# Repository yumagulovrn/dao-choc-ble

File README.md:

# Dao Choc BLE Keyboard

Dao Choc BLE keyboard is an ergonomic wireless split keyboard for Kailh Choc switches based on MINEW MS88SF2 BLE module. This split keyboard is similar to Corne but it has an extra keys for brackets and international layouts as on Jorne or Jian.

Available in 44 and 42 key variants

Inspiration for the keyboard was taken from these keyboards:
- [le_chiff_ble](https://github.com/MangoIV/le_chiff_ble) by [MangoIV](https://github.com/MangoIV) - electrical circuit
- [Corne](https://github.com/foostan/crkbd) by [foostan](https://github.com/foostan) - thumb cluster
- [Jorne](https://github.com/joric/jorne) by [joric](https://github.com/joric) - extra pinky key
- [Jian](https://github.com/KGOH/Jian-Info) by [KGOH](https://github.com/KGOH) - extra pinky key and column staggering
- [Coren-ish Zen](https://lowprokb.ca/products/corne-ish-zen) by [DarrylDH](https://github.com/LOWPROKB) - choc-spacing, vibes

## Features

- Hotswapabble
- Long battery life
- ZMK firmware
- Low profile
- Choc Spacing (18mm x 17mm)

## Firmware

Latest compiled ZMK firmware for this keyboard can be found here: https://github.com/yumagulovrn/dao-zmk-config/releases/latest

Source Code: https://github.com/yumagulovrn/dao-zmk-config

## Bootloader

Latest compiled bootloader based on Adafruit nRF52 Bootloader can be found here: https://github.com/yumagulovrn/Adafruit_nRF52_Bootloader/releases/latest

Source code: https://github.com/yumagulovrn/Adafruit_nRF52_Bootloader/tree/dao

You will need separate device to flash the bootloader.

Guide "how to flash the bootloader" can be found [here](https://github.com/Ladniy/jiran-ble-lite/wiki/Firmware). You can literally follow these instructions step-by-step but with *.hex file from [here](https://github.com/yumagulovrn/Adafruit_nRF52_Bootloader/releases/latest)

## Gerbers

https://github.com/yumagulovrn/dao-choc-ble/releases/latest

## BOM

### PCB

| Reference    | Name                      | Package  | Value           | AliExpress                                                                                                                                                                      | LCSC    | Qty |
|--------------|---------------------------|----------|-----------------|---------------------------------------------------------------------------------------------------------------------------------------------------------------------------------|---------|-----|
| BT1          | JST                       | ?        | 1.25mm 2pin 90° | [1.25mm 2pin 90° 50 pcs](https://aliexpress.com/item/10000064127272.html?sku_id=20000000117379413)                                                                              | ?       | 2   |
| C1-C2, C4-C5 | Capacitor                 | 0603     | 10uF            | [10uF - 100 pcs](https://aliexpress.com/item/32966526545.html?sku_id=66569661174)                                                                                               | C19702  | 8   |
| C3           | Capacitor                 | 0603     | 1nF             | [1nF - 100 pcs](https://aliexpress.com/item/32966526545.html?sku_id=66569661147)                                                                                                | C1588   | 2   |
| C6-C7        | Capacitor                 | 0603     | 4.7uF           | [4.7uF 100 pcs](https://aliexpress.com/item/32966526545.html?sku_id=66569661173)                                                                                                | C19666  | 4   |
| D1-D22       | Diode                     | SOD-323  | 1N4148WS        | [1N4148WS SOD-323 - 100 pcs](https://aliexpress.com/item/32849879904.html?sku_id=65195962305)                                                                                   | C57759  | 44  |
| D23          | Diode                     | SOD-123  | 1N5819W         | [1N5819W SOD-123 - 100 pcs](https://aliexpress.com/item/32849879904.html?sku_id=65195962304)                                                                                    | C169540 | 2   |
| D24          | LED                       | 0603     | RED             | [0603 RED - 100 pcs](https://aliexpress.com/item/1206456185.html?sku_id=65106628406)                                                                                            | C2286   | 2   |
| D25          | LED                       | 0603     | BLUE            | [0603 BLUE - 100 pcs](https://aliexpress.com/item/1206456185.html?sku_id=65106628409)                                                                                           | C72041  | 2   |
| F1           | Fuse                      | 1206     | 500mA           | [1206 500mA - 50 pcs](https://aliexpress.com/item/32907456681.html?sku_id=12000033093354867)                                                                                          | C355568 | 2   |
| J1           | USB Receptacle            | ?        | ?               | [1.6mm - 10 pcs](https://aliexpress.com/item/32998900371.html?sku_id=12000021526913497) [0.8mm - 10 pcs](https://aliexpress.com/item/32998900371.html?sku_id=12000021526913496) | C168688 | 2   |
| K1-K22       | Kailh Choc Hotswap Socket | ?        | ?               | [90 pcs](https://aliexpress.com/item/33023283633.html?sku_id=10000000883911874)                                                                                                 | ?       | 44  |
| Q1           | P-Mosfet                  | SOT-23   | AO3401A         | [50 pcs](https://aliexpress.com/item/32990534792.html)                                                                                                                          | C15127  | 2   |
| R1-R2        | Resistor                  | 0603     | 5.1k            | [5.1K - 100 pcs](https://aliexpress.com/item/1005001436923851.html?sku_id=12000016109475028)                                                                                    | C23186  | 4   |
| R3           | Resistor                  | 0603     | 4.7             | [4.7R - 100 pcs](https://aliexpress.com/item/1005001436923851.html?sku_id=12000016109357956)                                                                                    | C23164  | 2   |
| R4           | Resistor                  | 0603     | 1M              | [1M - 100 pcs](https://aliexpress.com/item/1005001436923851.html?sku_id=12000016109475082)                                                                                      | C22935  | 2   |
| R5           | Resistor                  | 0603     | **806k***       | [820K - 100pcs](https://aliexpress.com/item/1005001436923851.html?sku_id=12000016109475080)                                                                                     | C103828 | 2   |
| R6-R7        | Resistor                  | 0603     | 1k              | [1K - 100pcs](https://aliexpress.com/item/1005001436923851.html?sku_id=12000016109475011)                                                                                       | C21190  | 4   |
| R8           | Resistor                  | 0603     | 2M              | [2M - 100pcs](https://aliexpress.com/item/1005001436923851.html?sku_id=12000016109475089)                                                                                       | C22976  | 2   |
| R9           | Resistor                  | 0603     | **RPROG****     | [3.3K - 100pcs](https://aliexpress.com/item/1005001436923851.html?sku_id=12000016109475023)                                                                                     | C22978  | 2   |
| R10          | Resistor                  | 0603     | 100k            | [100K - 100pcs](https://aliexpress.com/item/1005001436923851.html?sku_id=12000016109475058)                                                                                     | C25803  | 2   |
| SW1          | SPDT Switch               | ?        | MSK-12C02       | [50 pcs](https://aliexpress.com/item/4000685483225.html?sku_id=12000020983019153)                                                                                               | C431541 | 2   |
| SW2          | Tactile Button            | ?        | TS-1086E        | [100 pcs](https://aliexpress.com/item/1005001846404680.html)                                                                                                                    | C455276 | 2   |
| U1           | MCU                       | ?        | MINEW MS88SF2   | [1 pcs](https://aliexpress.com/item/4000101935456.html)                                                                                                                      | ?       | 2   |
| U2           | ESD Protection IC         | SOT-23-6 | USBLC6-2SC6     | [USBLC6-2SC6 - 10 pcs](https://aliexpress.com/item/32523780535.html?sku_id=12000027513378590)                                                                                   | C558442 | 2   |
| U3           | Voltage Regulator IC      | SOT-23-5 | XC6220          | [30 pcs](https://aliexpress.com/item/4000271612572.html)                                                                                                                        | C86534  | 2   |
| U4           | Battery Charging IC       | SOT-23-5 | MCP73831        | [10 pcs](https://aliexpress.com/item/32714249253.html)                                                                                                                          | C14879  | 2   |

**806k*** You can replace it with 820k resistor, but voltage sensing circuit (for battery status) will give somewhat invalid values

**RPROG**** Value depends on your battery capacity. For 300mAh battery should be 3.3K

### Other hardware

| Name                           | Qty  | AliExpress                                                                                                                                                 |
|--------------------------------|------|------------------------------------------------------------------------------------------------------------------------------------------------------------|
| LiPo Battery 502035            |    2 | [Global - 2 pcs](https://aliexpress.com/item/1005003717206039.html?sku_id=12000026915285813) [RU - 1 pcs](https://www.chipdip.ru/product/robiton-lp502035) |
| Standoff M2x5mm                |   10 | [M2x5mm - 20 pcs](https://aliexpress.com/item/32597776358.html?sku_id=67114100494)                                                                         |
| Standoff M2x8mm                |    6 | [M2x8mm - 20 pcs](https://aliexpress.com/item/32597776358.html?sku_id=67114100497)                                                                         |
| Screw M2x4mm                   |   32 | [Black M2x4mm - 50 pcs](https://aliexpress.com/item/32806166548.html?sku_id=66702152887)                                                                   |
| Connector JST 1.25mm 2pin Male |    2 | [20 pcs](https://aliexpress.com/item/4000076660477.html)                                                                                                   |
| Silicone Bumpers               | 8-10 | [100 pcs](https://aliexpress.com/item/32912066603.html)                                                                                                    |

## Cases

Dao has a pretty wide choice of cases.

### FR4 Case

Consists of:
* Bottom [42key](https://github.com/yumagulovrn/dao-choc-ble/releases/download/v1.0/pcb_42key-dao-choc-ble-bottom-gerber.zip) [44key](https://github.com/yumagulovrn/dao-choc-ble/releases/download/v1.0/pcb_44key-dao-choc-ble-bottom-gerber.zip)
* Plate [42key](https://github.com/yumagulovrn/dao-choc-ble/releases/download/v1.0/pcb_42key-dao-choc-ble-plate-gerber.zip) [44key](https://github.com/yumagulovrn/dao-choc-ble/releases/download/v1.0/pcb_44key-dao-choc-ble-plate-gerber.zip)
* [Shield](https://github.com/yumagulovrn/dao-choc-ble/releases/download/v1.0/pcb_dao-choc-ble-shield-gerber.zip)

**Note: plate should be 1.2mm thickness, bottom and shield can be any thickness you want (but I suggest 1.6mm)**

### 3D Printed Cases

#### OpenSCAD case from [shirokovroma](https://github.com/shirokovroma)

Has two variants:
* Bumper (you would need to have FR4 or printed plate, bottom and shield)
  * 42 keys [left](https://github.com/yumagulovrn/dao-choc-ble/releases/download/v1.0/3d_42key-bumper-left.stl) [right](https://github.com/yumagulovrn/dao-choc-ble/releases/download/v1.0/3d_42key-bumper-right.stl)
  * 44 keys [left](https://github.com/yumagulovrn/dao-choc-ble/releases/download/v1.0/3d_44key-bumper-left.stl) [right](https://github.com/yumagulovrn/dao-choc-ble/releases/download/v1.0/3d_44key-bumper-right.stl)
* Full (you would need to have FR4 or printed plate and shield)
  * 42 keys [left](https://github.com/yumagulovrn/dao-choc-ble/releases/download/v1.0/3d_42key-case-left.stl) [right](https://github.com/yumagulovrn/dao-choc-ble/releases/download/v1.0/3d_42key-case-right.stl)
  * 44 keys [left](https://github.com/yumagulovrn/dao-choc-ble/releases/download/v1.0/3d_44key-case-left.stl) [right](https://github.com/yumagulovrn/dao-choc-ble/releases/download/v1.0/3d_44key-case-right.stl)

#### [Dao keyboard slim case by Grigory Pavlichenko](https://www.thingiverse.com/thing:5988122)

### CNC cases

#### [Dao Shield by Mposiblee](https://github.com/Mposiblee/DaoShield)

## To Do List
- [x] Add BOM
- [x] Add images
- [x] Add descriptions
- [x] Add references to inspiration sources
- [x] Add link to a firmware
- [x] Add link to a bootloader
- [x] Make release v1.0

## Contacts

Telegram: https://ergonautkb.t.me

Telegram (ru): https://ergonautkb_ru.t.me

## Support and Warranty

lmao

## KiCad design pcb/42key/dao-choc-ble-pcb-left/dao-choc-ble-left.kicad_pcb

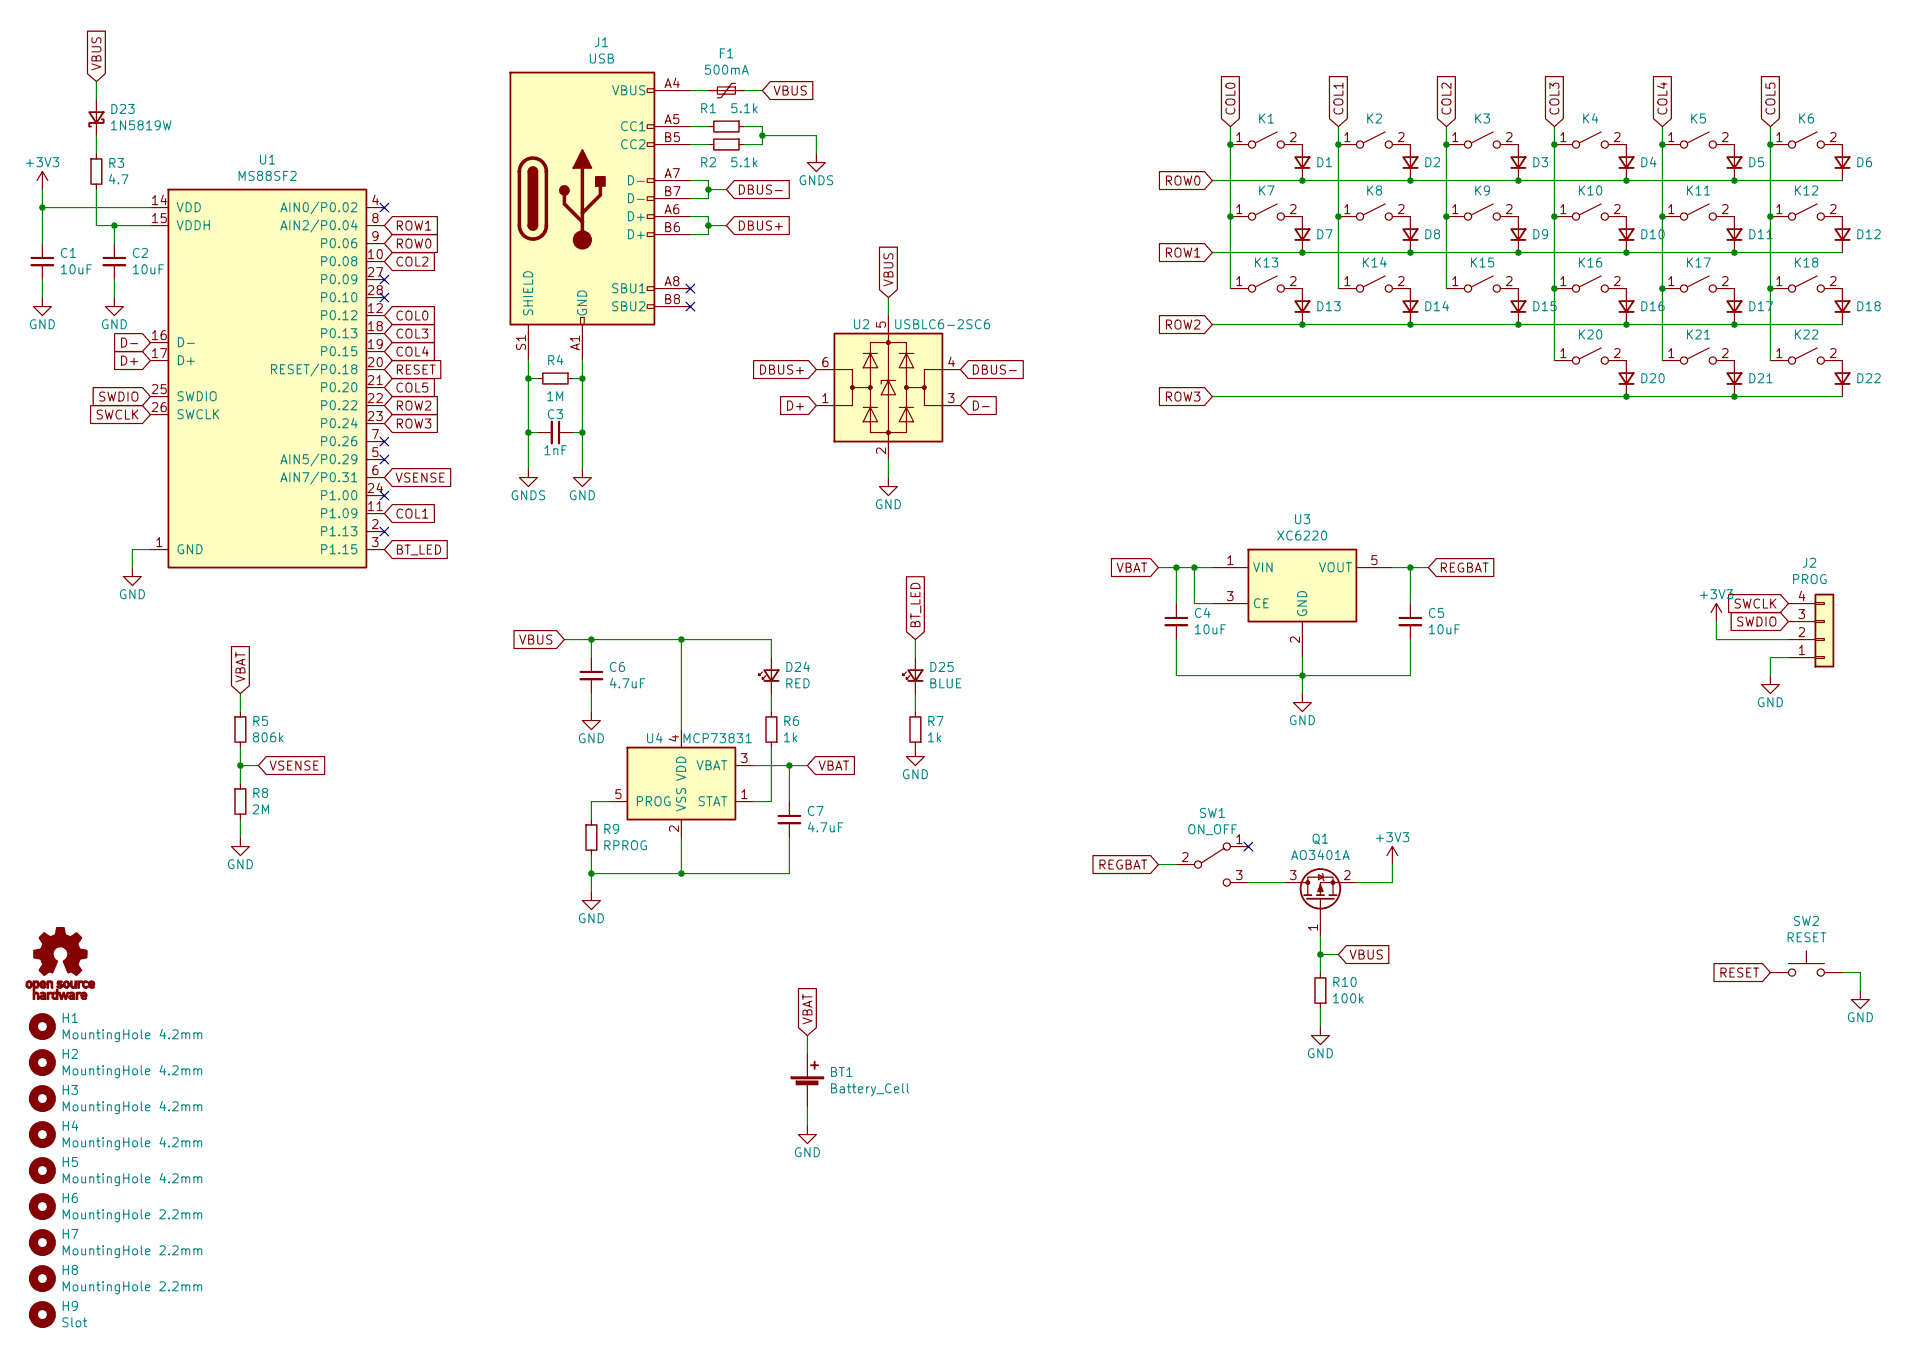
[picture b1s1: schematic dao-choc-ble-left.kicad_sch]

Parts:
BT1: Battery_Cell; Battery
C1, C2, C4, C5: 10uF; C_0603_1608Metric; LCSC C19702
C3: 1nF; C_0603_1608Metric; LCSC C1588
C6, C7: 4.7uF; C_0603_1608Metric; LCSC C19666
D1, D2, D3, D4, D5, D6, D7, D8, D9, D10, D11, D12, D13, D14, D15, D16, D17, D18, D20, D21, D22: 1N4148WS; D_SOD-323; LCSC C57759
D23: 1N5819W; D_SOD-123; LCSC C169540
D24: RED; LED_0603_1608Metric; LCSC C2286
D25: BLUE; LED_0603_1608Metric; LCSC C72041
F1: 500mA; Fuse_1206_3216Metric; LCSC C355568
H1, H2, H3, H4, H5: MountingHole 4.2mm; Hole_4.2mm
H6, H7, H8: MountingHole 2.2mm; Hole_2.2mm
H9: Slot
J1: USB; USB-C_C168688; LCSC C168688
J2: PROG
K1, K2, K3, K4, K5, K6, K7, K8, K9, K10, K11, K12, K13, K14, K15, K16, K17, K18, K20, K21, K22: KEY_SWITCH; Kailh_PG1350_hotswap
LOGO1: OSHW-logo
Q1: AO3401A; SOT-23; LCSC C15127
R1, R2: 5.1k; R_0603_1608Metric; LCSC C23186
R3: 4.7; R_0603_1608Metric; LCSC C23164
R4: 1M; R_0603_1608Metric; LCSC C22935
R5: 806k; R_0603_1608Metric; LCSC C103828
R6, R7: 1k; R_0603_1608Metric; LCSC C21190
R8: 2M; R_0603_1608Metric; LCSC C22976
R9: RPROG; R_0603_1608Metric; LCSC C22978
R10: 100k; R_0603_1608Metric; LCSC C25803
SW1: ON_OFF; MSK-12C02; LCSC C431541
SW2: RESET; TS-1086E; LCSC C455276
U1: MS88SF2; MINEW_MS88SF2
U2: USBLC6-2SC6; SOT-23-6; LCSC C558442
U3: XC6220; SOT-23-5; LCSC C86534
U4: MCP73831; SOT-23-5; LCSC C14879

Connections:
+3V3: C1.1, J2.2, Q1.2 (S), U1.14 (VDD)
BT_LED: D25.2 (A), U1.3 (P1.15)
COL0: K1.1 (A), K7.1 (A), K13.1 (A), U1.12 (P0.12)
COL1: K2.1 (A), K8.1 (A), K14.1 (A), U1.11 (P1.09)
COL2: K3.1 (A), K9.1 (A), K15.1 (A), U1.10 (P0.08)
COL3: K4.1 (A), K10.1 (A), K16.1 (A), K20.1 (A), U1.18 (P0.13)
COL4: K5.1 (A), K11.1 (A), K17.1 (A), K21.1 (A), U1.19 (P0.15)
COL5: K6.1 (A), K12.1 (A), K18.1 (A), K22.1 (A), U1.21 (P0.20)
D+: U1.17 (D+), U2.1 (I/O1)
D-: U1.16 (D-), U2.3 (I/O2)
DBUS+: J1.A6 (D+), J1.B6 (D+), U2.6 (I/O1)
DBUS-: J1.A7 (D-), J1.B7 (D-), U2.4 (I/O2)
GND: BT1.2 (-), C1.2, C2.2, C3.1, C4.2, C5.2, C6.2, C7.2, J1.A1 (GND), J1.A12 (GND), J1.B1 (GND), J1.B12 (GND), J2.1, R4.1, R7.1, R8.2, R9.2, R10.1, SW2.2, U1.1 (GND), U1.13 (GND), U2.2 (GND), U3.2 (GND), U4.2 (VSS)
GNDS: C3.2, J1.S1 (SHIELD), R1.1, R2.1, R4.2
unnamed: C2.1, R3.2, U1.15 (VDDH)
unnamed: D1.2 (A), K1.2 (B)
unnamed: D2.2 (A), K2.2 (B)
unnamed: D3.2 (A), K3.2 (B)
unnamed: D4.2 (A), K4.2 (B)
unnamed: D5.2 (A), K5.2 (B)
unnamed: D6.2 (A), K6.2 (B)
unnamed: D7.2 (A), K7.2 (B)
unnamed: D8.2 (A), K8.2 (B)
unnamed: D9.2 (A), K9.2 (B)
unnamed: D10.2 (A), K10.2 (B)
unnamed: D11.2 (A), K11.2 (B)
unnamed: D12.2 (A), K12.2 (B)
unnamed: D13.2 (A), K13.2 (B)
unnamed: D14.2 (A), K14.2 (B)
unnamed: D15.2 (A), K15.2 (B)
unnamed: D16.2 (A), K16.2 (B)
unnamed: D17.2 (A), K17.2 (B)
unnamed: D18.2 (A), K18.2 (B)
unnamed: D20.2 (A), K20.2 (B)
unnamed: D21.2 (A), K21.2 (B)
unnamed: D22.2 (A), K22.2 (B)
unnamed: D23.1 (K), R3.1
unnamed: D24.1 (K), R6.2
unnamed: D25.1 (K), R7.2
unnamed: F1.2, J1.A4 (VBUS), J1.A9 (VBUS), J1.B4 (VBUS), J1.B9 (VBUS)
unnamed: J1.A5 (CC1), R1.2
unnamed: J1.B5 (CC2), R2.2
unnamed: Q1.3 (D), SW1.3 (C)
unnamed: R6.1, U4.1 (STAT)
unnamed: R9.1, U4.5 (PROG)
REGBAT: C5.1, SW1.2 (B), U3.5 (VOUT)
RESET: SW2.1, U1.20 (RESET/P0.18)
ROW0: D1.1 (K), D2.1 (K), D3.1 (K), D4.1 (K), D5.1 (K), D6.1 (K), U1.9 (P0.06)
ROW1: D7.1 (K), D8.1 (K), D9.1 (K), D10.1 (K), D11.1 (K), D12.1 (K), U1.8 (AIN2/P0.04)
ROW2: D13.1 (K), D14.1 (K), D15.1 (K), D16.1 (K), D17.1 (K), D18.1 (K), U1.22 (P0.22)
ROW3: D20.1 (K), D21.1 (K), D22.1 (K), U1.23 (P0.24)
SWCLK: J2.4, U1.26 (SWCLK)
SWDIO: J2.3, U1.25 (SWDIO)
VBAT: BT1.1 (+), C4.1, C7.1, R5.1, U3.1 (VIN), U3.3 (CE), U4.3 (VBAT)
VBUS: C6.1, D23.2 (A), D24.2 (A), F1.1, Q1.1 (G), R10.2, U2.5 (VBUS), U4.4 (VDD)
VSENSE: R5.2, R8.1, U1.6 (AIN7/P0.31)

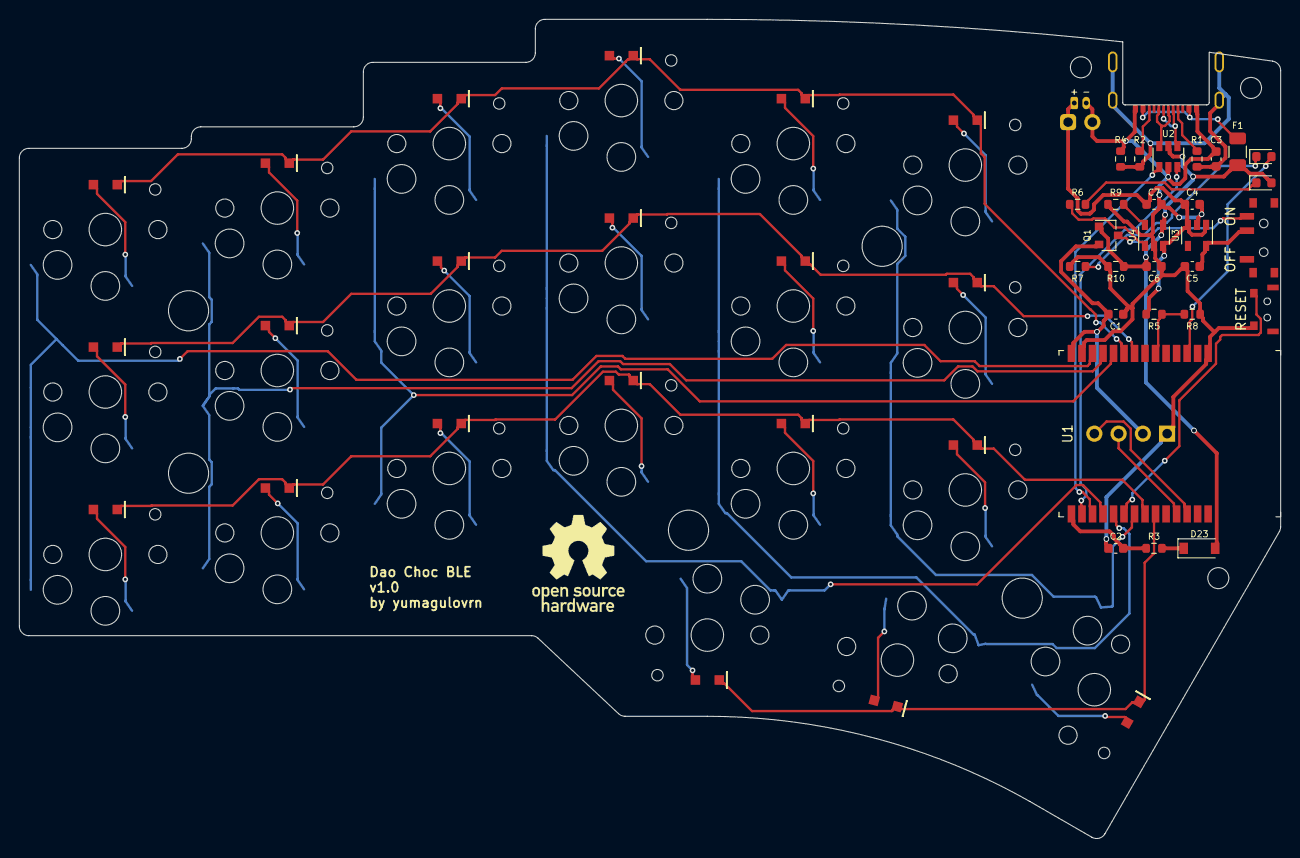
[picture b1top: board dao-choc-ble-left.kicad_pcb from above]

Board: 2 copper layers, 132.0 x 85.7 mm, 82 parts (1 on the bottom side), 56 nets.

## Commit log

2021-10-17 feature: changed footprint for battery connector
2021-11-28 Add images, description and references information
2021-12-16 feat: added links to bootloader and firmware
2022-01-01 feat: added 42key variant and BOM
2022-01-08 Add more AliExpress links
2022-01-08 Fix errors
2022-01-08 Change region of AliExpress links
2022-01-08 Add 806k resistor information
2022-01-08 Fix line break
2022-01-16 scad body source files
2022-01-16 scad case stl
2022-01-19 Added 42 key variant for the 3d case + refactor
2022-01-19 Fixed formatting
2022-07-24 fix: updated BOM
2022-07-24 feat: update links in BOM
2022-07-24 fix: fixed hardware links
2022-07-24 feat: added bootloader flashing guide link
2022-07-24 fix: fixed typo in inspiration section
2022-08-05 Update README.md
    fix count pcs
2023-09-01 Readme update

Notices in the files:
pcb/42key/dao-choc-ble-pcb-left/dao-choc-ble-left.kicad_pcb:
Copyright (c) 2021
Licensed under CERN-OHL-P v2
